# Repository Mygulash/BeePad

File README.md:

# 🐝BeePad
Hackpad project from Hack Club

Beepad is a macropad with 9 switches, rotary encoder and OLED display. It runs KMK firmware. 
***
## Features: 
- 9 keys
- 128×32 OLED display
- Rotary encoder
***
## CAD model
Everything fits together using 6 M3 bolts and heat-set inserts.

It consists of 2 printed parts: 
- Top
- Bottom

Made using AutoDesk Fusion

***
## PCB
Designed in KiCAD

**Schematic:**

**PCB:**

***
## BOM:
- 9x Cherry MX Switches
- 9x DSA Keycaps
- 6x M3x5x4 Heatset inserts
- 6x M3x16mm SHCS Bolts
- 9x 1N4148 DO-35 Diodes.
- 1x 0.91" 128x32 OLED Display
- 1x EC11 Rotary Encoder
- 1x XIAO RP2040
- 1x Case (2 printed parts)

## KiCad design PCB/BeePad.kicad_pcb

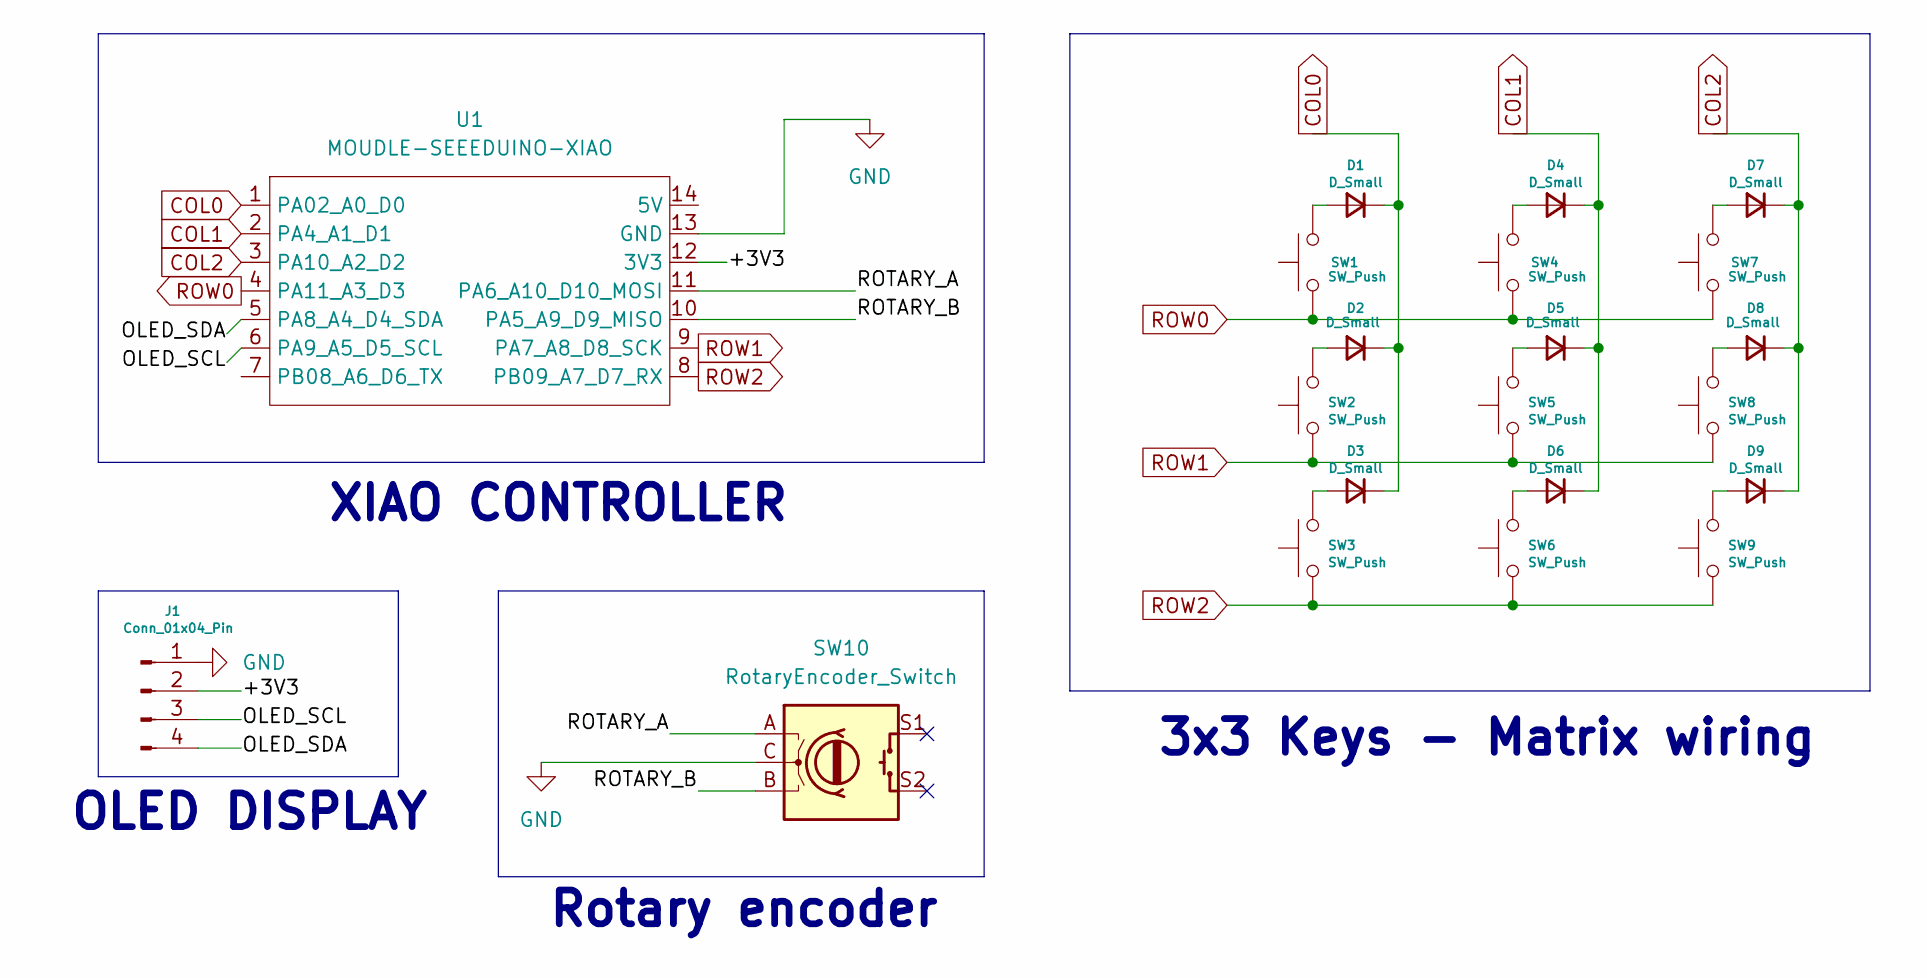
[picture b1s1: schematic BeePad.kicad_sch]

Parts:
D1, D2, D3, D4, D5, D6, D7, D8, D9: D_Small; D_DO-35_SOD27_P7.62mm_Horizontal
J1: Conn_01x04_Pin; SSD1306-0.91-OLED-4pin-128x32
SW1, SW2, SW3, SW4, SW5, SW6, SW7, SW8, SW9: SW_Push; SW_Cherry_MX_1.00u_PCB
SW10: RotaryEncoder_Switch; RotaryEncoder_Alps_EC11E-Switch_Vertical_H20mm
U1: MOUDLE-SEEEDUINO-XIAO; XIAO-Generic-Hybrid-14P-2.54-21X17.8MM

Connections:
/+3V3: J1.2, U1.12 (3V3)
/OLED_SCL: J1.3, U1.6 (PA9_A5_D5_SCL)
/OLED_SDA: J1.4, U1.5 (PA8_A4_D4_SDA)
/ROTARY_A: SW10.A, U1.11 (PA6_A10_D10_MOSI)
/ROTARY_B: SW10.B, U1.10 (PA5_A9_D9_MISO)
COL0: D1.1 (K), D2.1 (K), D3.1 (K), U1.1 (PA02_A0_D0)
COL1: D4.1 (K), D5.1 (K), D6.1 (K), U1.2 (PA4_A1_D1)
COL2: D7.1 (K), D8.1 (K), D9.1 (K), U1.3 (PA10_A2_D2)
GND: J1.1, SW10.C, U1.13 (GND)
unnamed: D1.2 (A), SW1.2
unnamed: D2.2 (A), SW2.2
unnamed: D3.2 (A), SW3.2
unnamed: D4.2 (A), SW4.2
unnamed: D5.2 (A), SW5.2
unnamed: D6.2 (A), SW6.2
unnamed: D7.2 (A), SW7.2
unnamed: D8.2 (A), SW8.2
unnamed: D9.2 (A), SW9.2
ROW0: SW1.1, SW4.1, SW7.1, U1.4 (PA11_A3_D3)
ROW1: SW2.1, SW5.1, SW8.1, U1.9 (PA7_A8_D8_SCK)
ROW2: SW3.1, SW6.1, SW9.1, U1.8 (PB09_A7_D7_RX)

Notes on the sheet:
OLED DISPLAY
XIAO CONTROLLER
3x3 Keys - Matrix wiring
Rotary encoder

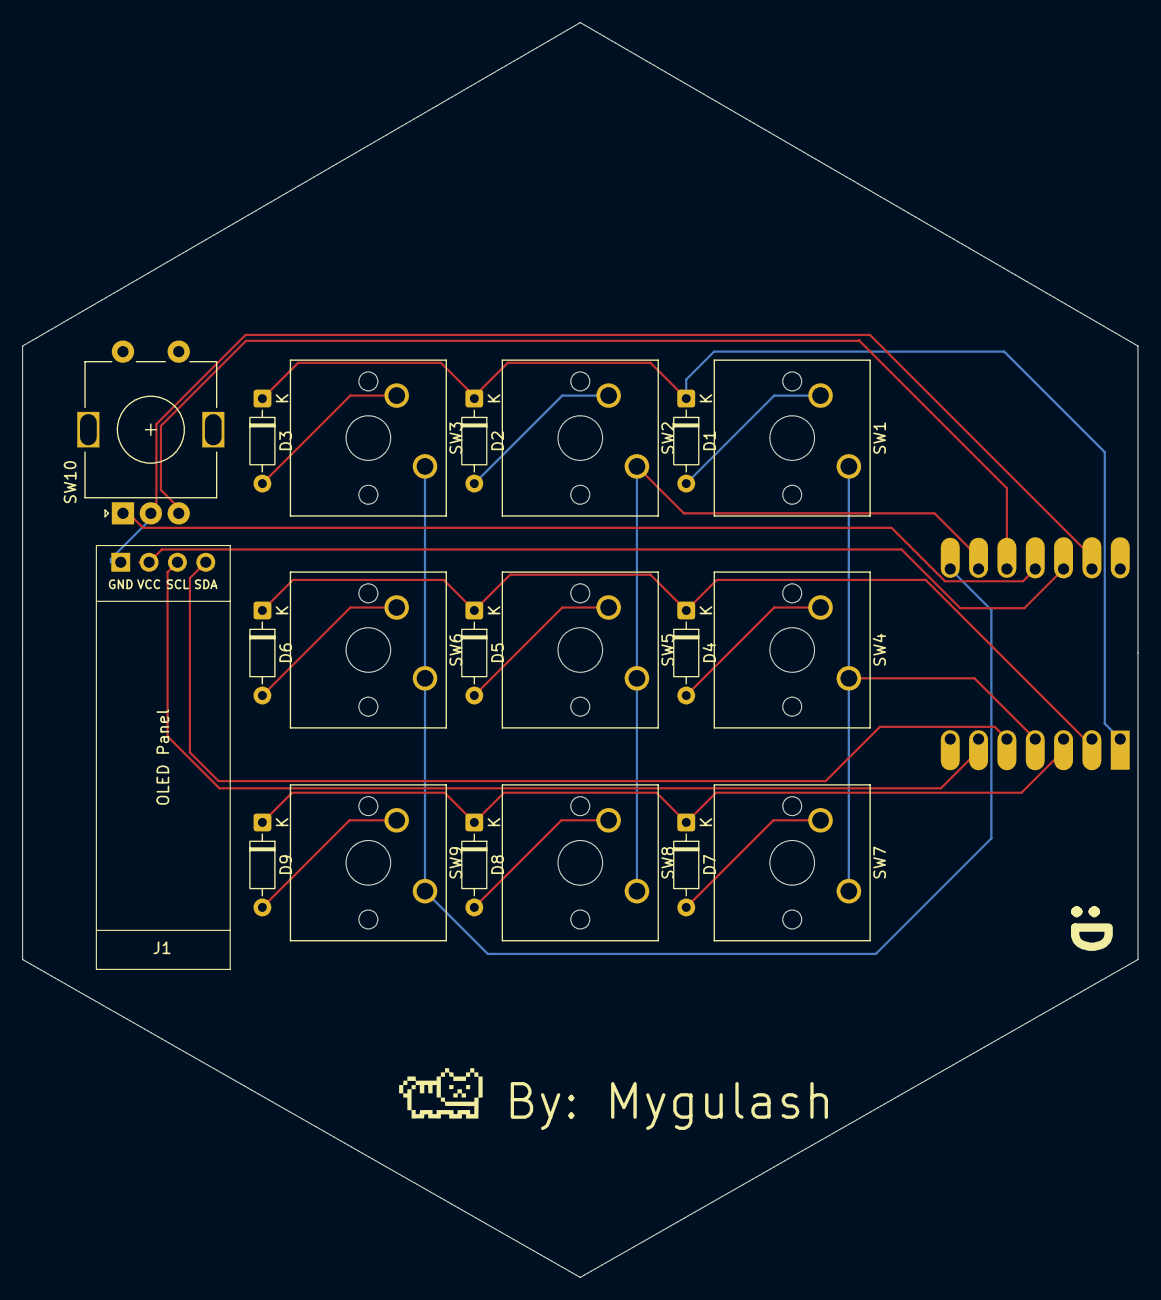
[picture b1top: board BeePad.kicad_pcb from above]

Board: 2 copper layers, 100.0 x 112.5 mm, 21 parts (1 on the bottom side), 21 nets.
